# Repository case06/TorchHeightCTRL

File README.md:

# TorchHeightCTRL
Capacitive height-controller for the OpenSourceEcology.org TorchTable

<p></p>

see also http://opensourceecology.org/wiki/CNC_Torch_Table_Height_Controller

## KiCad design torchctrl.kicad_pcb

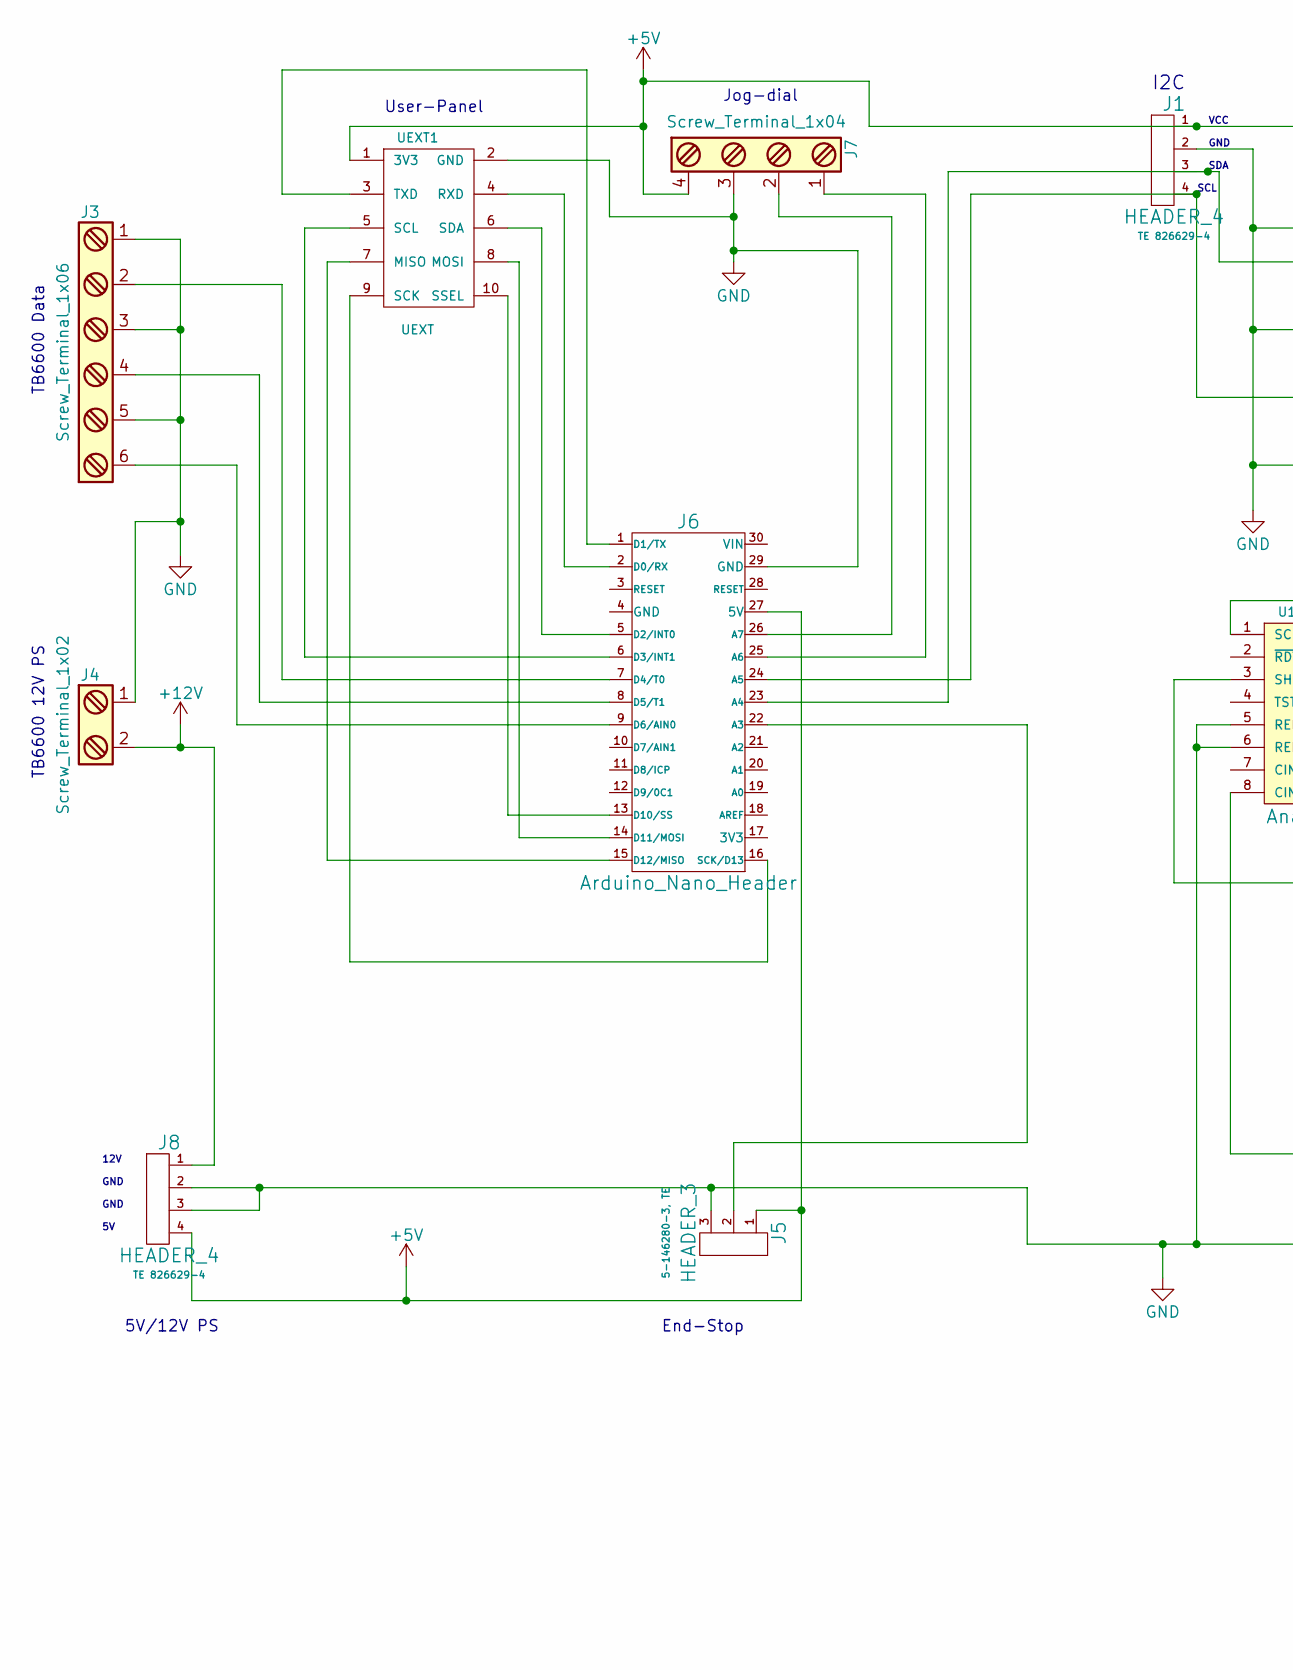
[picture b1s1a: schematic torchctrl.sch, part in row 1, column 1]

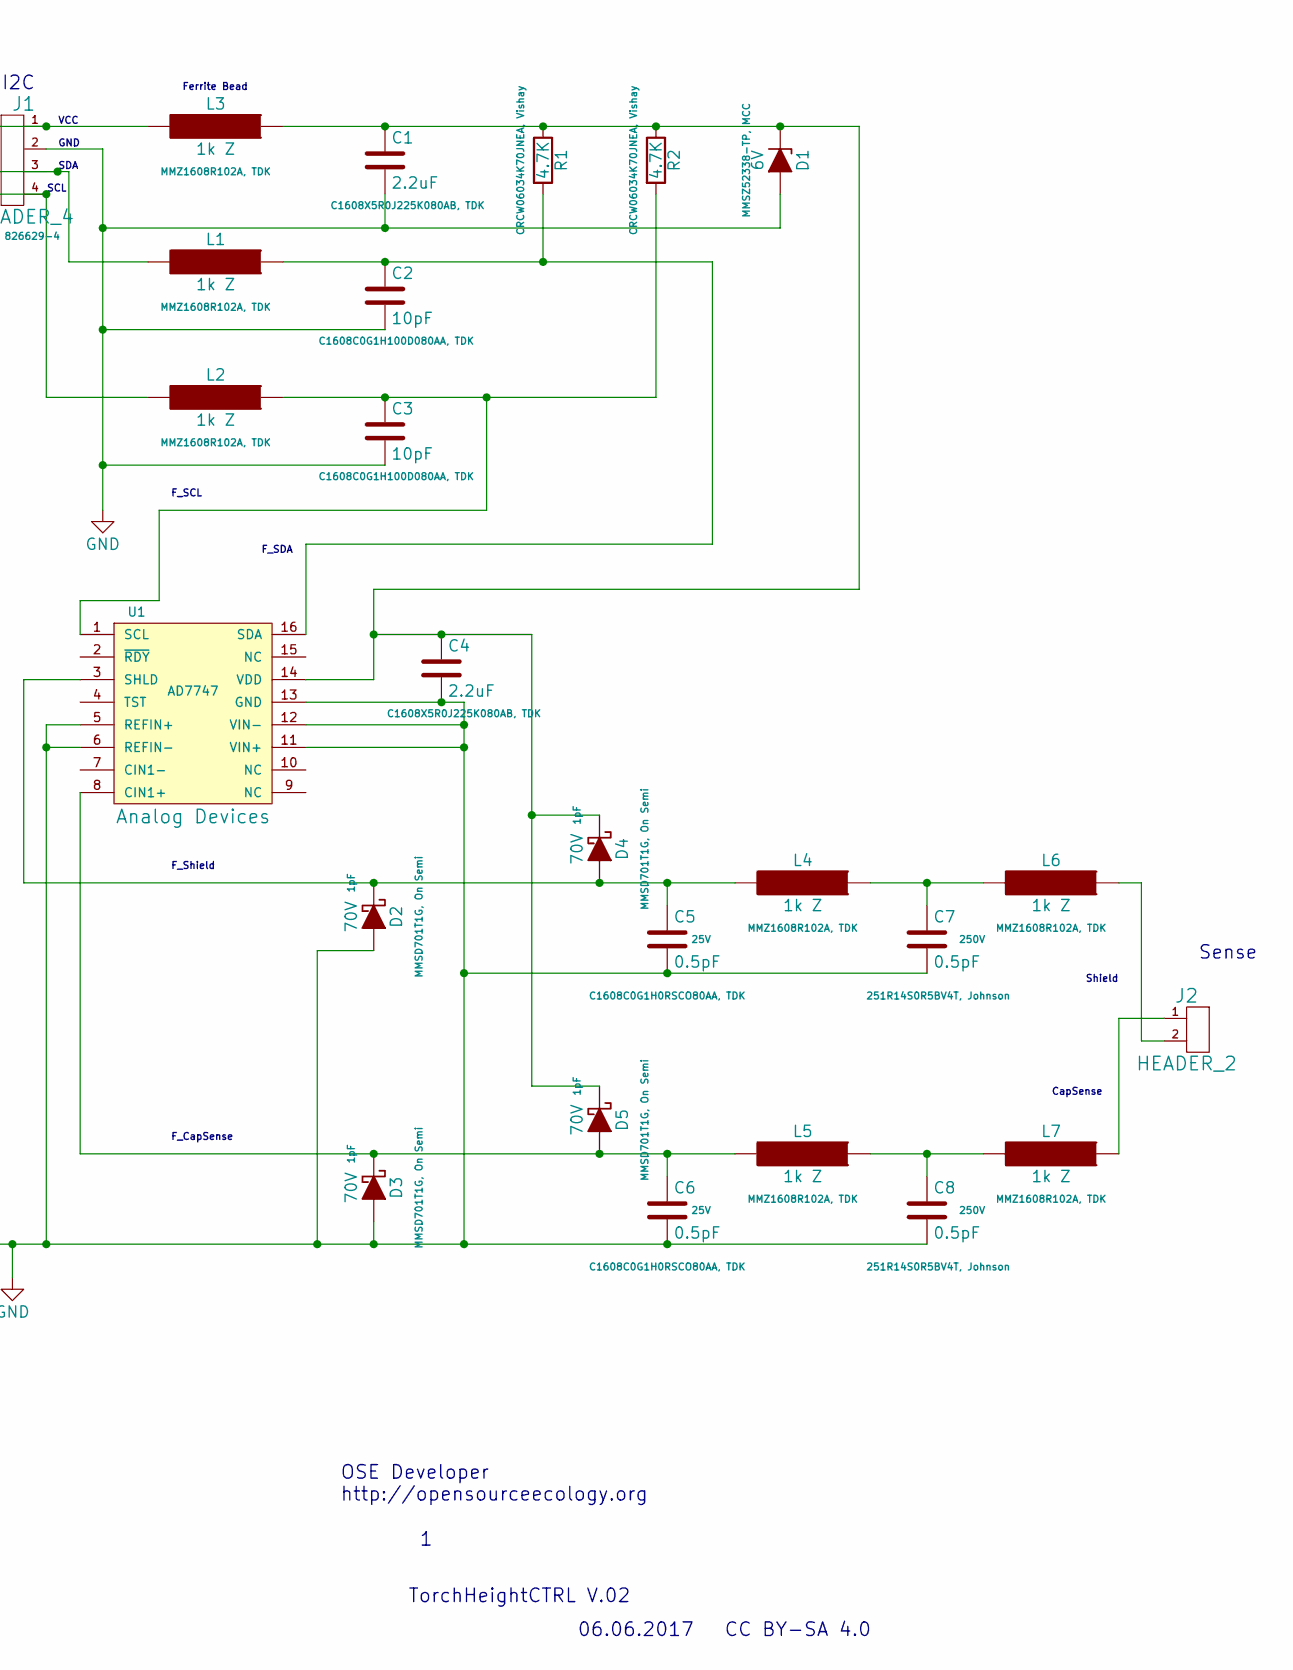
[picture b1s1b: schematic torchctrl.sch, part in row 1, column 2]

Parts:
C1, C4: 2.2uF; c_0603
C2, C3: 10pF; c_0603
C5, C6, C7, C8: 0.5pF; c_0603
D1: 6V; sod123
D2, D3, D4, D5: 70V; sod123
J1: HEADER_4; Pin_Header_Straight_1x04
J2: HEADER_2; bnc_90_1-1337543-0
J3: Screw_Terminal_1x06; mpt_0,5%2f6-2,54
J4: Screw_Terminal_1x02; mpt_0,5%2f2-2,54
J5: HEADER_3; Pin_Header_Straight_1x03
J6: Arduino_Nano_Header; arduino_mini
J7: Screw_Terminal_1x04; mpt_0,5%2f4-2,54
J8: HEADER_4; conn_hdd_15-24-4449
L1, L2, L3, L4, L5, L6, L7: 1k Z; r_0603
R1, R2: 4.7K; r_0603
U1: AD7747; tssop-16
UEXT1: UEXT; vasch_strip_5x2

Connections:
+5V: J1.1, J5.1, J6.27 (5V), J7.4, J8.4, L3.2, UEXT1.1 (3V3)
+12V: J4.2, J8.1
GND: C1.2, C2.2, C3.2, C4.2, C5.2, C6.2, C7.2, C8.2, D1.2 (A), D2.2 (A), D3.2 (A), J1.2, J3.1, J3.3, J3.5, J4.1, J5.3, J6.29 (GND), J7.3, J8.2, J8.3, U1.5 (REFIN+), U1.6 (REFIN-), U1.11 (VIN+), U1.12 (VIN-), U1.13 (GND), UEXT1.2 (GND)
unnamed: C1.1, C4.1, D1.1 (K), D4.1 (K), D5.1 (K), L3.1, R1.1, R2.1, U1.14 (VDD)
unnamed: C2.1, L1.1, R1.2, U1.16 (SDA)
unnamed: C3.1, L2.1, R2.2, U1.1 (SCL)
unnamed: C5.1, D2.1 (K), D4.2 (A), L4.2, U1.3 (SHLD)
unnamed: C6.1, D3.1 (K), D5.2 (A), L5.2, U1.8 (CIN1+)
unnamed: C7.1, L4.1, L6.2
unnamed: C8.1, L5.1, L7.2
unnamed: J1.3, J6.23 (A4), L1.2
unnamed: J1.4, J6.24 (A5), L2.2
unnamed: J2.1, L7.1
unnamed: J2.2, L6.1
unnamed: J3.2, J6.7 (D4/T0)
unnamed: J3.4, J6.8 (D5/T1)
unnamed: J3.6, J6.9 (D6/AIN0)
unnamed: J5.2, J6.22 (A3)
unnamed: J6.1 (D1/TX), UEXT1.3 (TXD)
unnamed: J6.2 (D0/RX), UEXT1.4 (RXD)
unnamed: J6.5 (D2/INT0), UEXT1.6 (SDA)
unnamed: J6.6 (D3/INT1), UEXT1.5 (SCL)
unnamed: J6.13 (D10/SS), UEXT1.10 (SSEL)
unnamed: J6.14 (D11/MOSI), UEXT1.8 (MOSI)
unnamed: J6.15 (D12/MISO), UEXT1.7 (MISO)
unnamed: J6.16 (SCK/D13), UEXT1.9 (SCK)
unnamed: J6.25 (A6), J7.1
unnamed: J6.26 (A7), J7.2

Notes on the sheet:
TorchHeightCTRL V.02
06.06.2017
OSE Developer http://opensourceecology.org
CC BY-SA 4.0
I2C
Ferrite Bead
Sense
CapSense
Shield
F_Shield
F_CapSense
F_SCL
F_SDA
VCC
GND
SDA
SCL
Jog-dial
TB6600 Data
TB6600 12V PS
User-Panel
End-Stop
5V/12V PS
12V

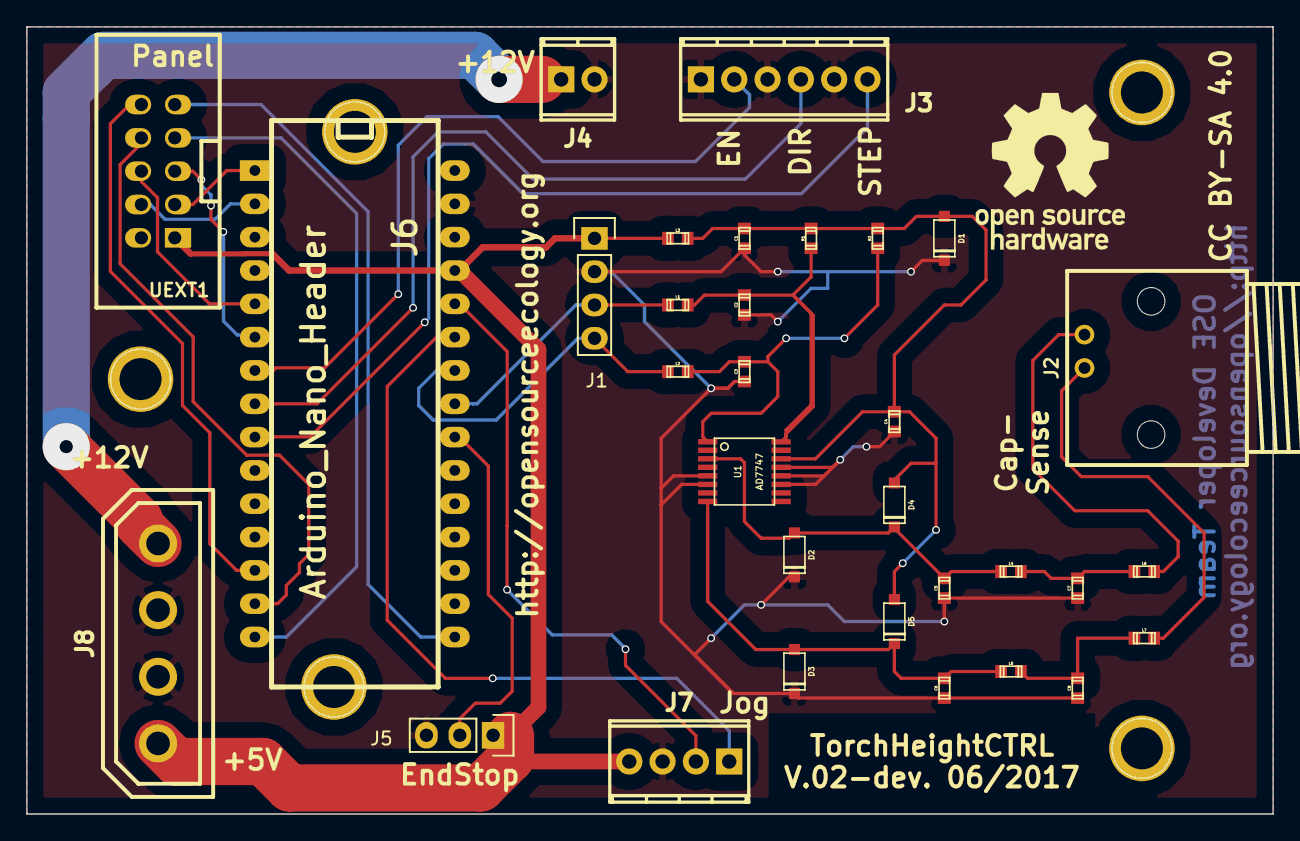
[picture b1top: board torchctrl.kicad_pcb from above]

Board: 2 copper layers, 95.0 x 60.0 mm, 32 parts (0 on the bottom side), 28 nets.

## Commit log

2017-06-07 minor changes
2017-06-07 add picture
2017-06-07 remove old backup file
2017-06-20 added gerber files
2017-06-20 added order-list for mouser in BOM
2017-06-25 added firmware for manually operated version
2017-07-22 Firmware for TorchHeightCTRL_V02k, auto-Version
2017-07-25 added host-monitoring-tool, written in Processing
2017-08-08 added button-press functionality for rotary encoder
2017-08-11 added EndStop functionality
2017-08-15 updated EndStop functionality with balancing
2017-10-12 changed path for 3d-parts from home into repo-lib
2017-10-12 changed layers on
2017-10-13 simple version
2017-10-14 changed manual/RAMPS version to Z-port instead of E0
